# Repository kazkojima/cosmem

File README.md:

# cosmem

cosmem is a simple RAM/ROM/clock generator for COSMAC 1802 CPU, implemnted with TinyFPGA. An ancient chip meets FPGA :-)

spimemio.v is imported from the picorv32 example written by Clifford Wolf.

[board]

lv3v3/ is for kicad files of a level shifter board to interface 1802 and TinyFPGA.

within this enclosure

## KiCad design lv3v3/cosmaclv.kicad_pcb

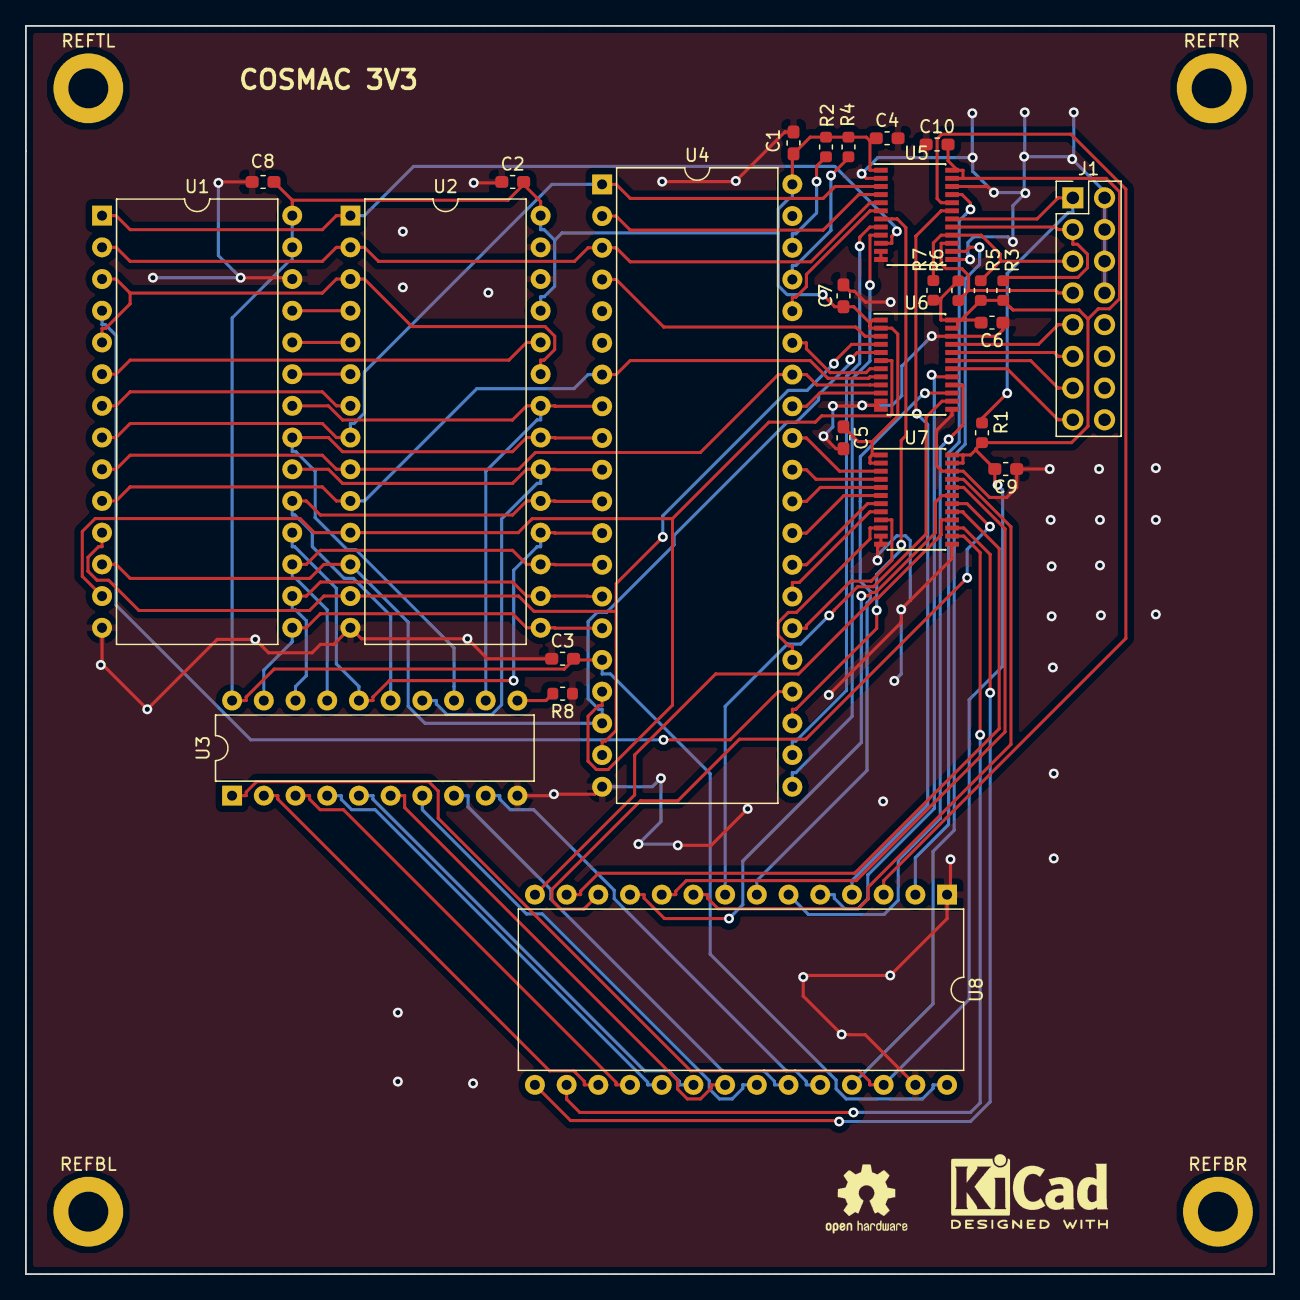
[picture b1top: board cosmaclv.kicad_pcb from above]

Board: 2 copper layers, 100.0 x 100.0 mm, 31 parts (0 on the bottom side), 77 nets.

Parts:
C1, C2, C3, C4, C5, C6, C7, C8, C9, C10: 0.1u; C_0603_1608Metric_Pad1.05x0.95mm_HandSolder
J1: Conn_02x08_Odd_Even; PinHeader_2x08_P2.54mm_Vertical
R1, R2, R3, R4, R5, R6, R7: 10k; R_0603_1608Metric
R8: 0; R_0603_1608Metric
REFBL: MountingHole_3.2mm_M3_DIN965_Pad
REFBR: MountingHole_3.2mm_M3_DIN965_Pad
REFTL: MountingHole_3.2mm_M3_DIN965_Pad
REFTR: MountingHole_3.2mm_M3_DIN965_Pad
U1, U2: CDP1855; DIP-28_W15.24mm
U3: FXMA108-BO; DIP-20_W7.62mm
U4: CDP1802; DIP-40_W15.24mm
U5, U6, U7: 74LVC8T245PW; TSSOP-24_4.4x7.8mm_P0.65mm
U8: TinyFPGA-BX; DIP-28_W15.24mm

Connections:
+3V3: C6.2, C9.2, C10.2, R1.1, R3.1, R5.1, R6.1, R7.1, U3.1, U5.23, U5.24, U6.23, U6.24, U7.23, U7.24, U8.26
+5V: C1.2, C2.2, C3.2, C4.1, C5.1, C7.1, C8.1, R2.1, R4.1, U1.27, U1.28, U2.25, U2.28, U3.20, U4.16, U4.40, U5.1, U6.1, U6.2, U7.1, U7.2, U8.28
CE: U5.14, U8.25
CLK: U1.8, U2.8, U4.1, U5.3
CLR: U1.2, U2.2, U4.3, U5.5
DB0: U3.2, U8.17
DB1: U3.3, U8.18
DB2: U3.4, U8.19
DB3: U3.5, U8.20
DB4: U3.6, U8.21
DB5: U3.7, U8.22
DB6: U3.8, U8.23
DB7: U3.9, U8.24
EF2: U4.23, U5.7
EF3: U4.22, U5.8
EF4: U4.21, U5.9
GND: C1.1, C2.1, C3.1, C4.2, C5.2, C6.1, C7.2, C8.2, C9.1, C10.1, J1.2, J1.4, J1.6, J1.8, R8.1, U1.14, U1.26, U2.14, U2.26, U2.27, U3.10, U4.20, U5.2, U5.11, U5.12, U5.13, U5.22, U6.11, U6.12, U6.13, U6.22, U7.11, U7.12, U7.13, U7.22, U8.1, U8.27
INT: U4.36, U5.6
MDU: U1.1, U2.1, U5.10
MRD: U1.10, U2.10, U4.7, U6.8
N0: U1.11, U2.13, U4.19, U6.4
N1: U1.12, U2.12, U4.18, U6.5
N2: U1.13, U2.11, U4.17, U6.6
unnamed: J1.1, R1.2, U5.18
unnamed: J1.3, R3.2, U5.17
unnamed: J1.5, R5.2, R7.2, U5.16
unnamed: J1.7, R6.2, U5.15
unnamed: J1.9, U6.21
unnamed: J1.11, U6.20
unnamed: J1.13, U6.19
unnamed: J1.15, U6.18
unnamed: R2.2, U4.38
unnamed: R4.2, U4.37
unnamed: R8.2, U3.11
unnamed: U1.3, U1.5, U2.3, U2.23
unnamed: U1.4, U4.24
unnamed: U1.6, U2.24
unnamed: U1.7, U2.7
unnamed: U1.15, U2.15, U3.19, U4.15
unnamed: U1.16, U2.16, U3.18, U4.14
unnamed: U1.17, U2.17, U3.17, U4.13
unnamed: U1.18, U2.18, U3.16, U4.12
unnamed: U1.19, U2.19, U3.15, U4.11
unnamed: U1.20, U2.20, U3.14, U4.10
unnamed: U1.21, U2.21, U3.13, U4.9
unnamed: U1.22, U2.22, U3.12, U4.8
unnamed: U1.23, U2.6
unnamed: U1.24, U2.5
unnamed: U1.25, U2.4
unnamed: U4.25, U7.10
unnamed: U4.26, U7.9
unnamed: U4.27, U7.8
unnamed: U4.28, U7.7
unnamed: U4.29, U7.6
unnamed: U4.30, U7.5
unnamed: U4.31, U7.4
unnamed: U4.32, U7.3
unnamed: U4.33, U6.10
unnamed: U4.35, U6.7
unnamed: U5.19, U8.4
unnamed: U5.20, U8.3
unnamed: U5.21, U8.2
unnamed: U6.14, U8.8
unnamed: U6.15, U8.7
unnamed: U6.16, U8.6
unnamed: U6.17, U8.5
unnamed: U7.14, U8.16
unnamed: U7.15, U8.15
unnamed: U7.16, U8.14
unnamed: U7.17, U8.13
unnamed: U7.18, U8.12
unnamed: U7.19, U8.11
unnamed: U7.20, U8.10
unnamed: U7.21, U8.9
Q: U4.4, U6.3
TBA: U1.9, U2.9, U4.34, U6.9
WAIT: U4.2, U5.4

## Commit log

2019-03-23 Initial commit.
2019-03-24 Fix thinko.
2019-03-30 Tiny test.
2019-03-31 Add flash loader.
2019-03-31 Add README.md
2019-03-31 Add kicad files to lv3v3.
2019-03-31 branch for images
2019-03-31 Update README.md.
2019-04-16 Add spimbox.
2019-06-09 Fix firmware.S.
2019-06-09 Add a box image.
2019-06-09 Adjust README.md.
